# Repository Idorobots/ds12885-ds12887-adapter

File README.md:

# DS12885 -> DS12887 adapter

Ever needed to retrofit a DS1285 compatible RTC in a DS1287 compatible slot? This board's got you covered.

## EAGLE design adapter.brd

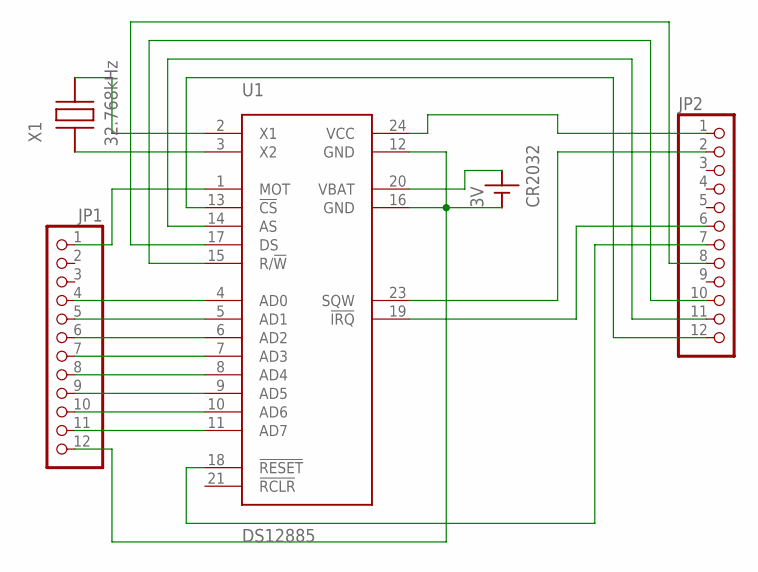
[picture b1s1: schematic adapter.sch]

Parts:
3V: CR2032; CR2032H
JP1, JP2: PINHD-1X12; 1X12
U1: DS12885; DIP24
X1: 32.768kHz; 2PAD

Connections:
GND: 3V.- (GND), JP1.12, U1.12 (GND), U1.16 (GND)
unnamed: U1.3 (X2), X1.2 (X1)
unnamed: U1.2 (X1), X1.1 (X2)
unnamed: JP1.1, U1.1 (MOT)
unnamed: JP1.4, U1.4 (AD0)
unnamed: JP1.5, U1.5 (AD1)
unnamed: JP1.6, U1.6 (AD2)
unnamed: JP1.7, U1.7 (AD3)
unnamed: JP1.8, U1.8 (AD4)
unnamed: JP1.9, U1.9 (AD5)
unnamed: JP1.10, U1.10 (AD6)
unnamed: JP1.11, U1.11 (AD7)
unnamed: 3V.+ (VCC), U1.20 (VBAT)
unnamed: JP2.1, U1.24 (VCC)
unnamed: JP2.2, U1.23 (SQW)
unnamed: JP2.6, U1.19 (!IRQ!)
unnamed: JP2.7, U1.18 (!RESET!)
unnamed: JP2.11, U1.14 (AS)
unnamed: JP2.12, U1.13 (!CS!)
unnamed: JP2.10, U1.15 (R/!W!)
unnamed: JP2.8, U1.17 (DS)

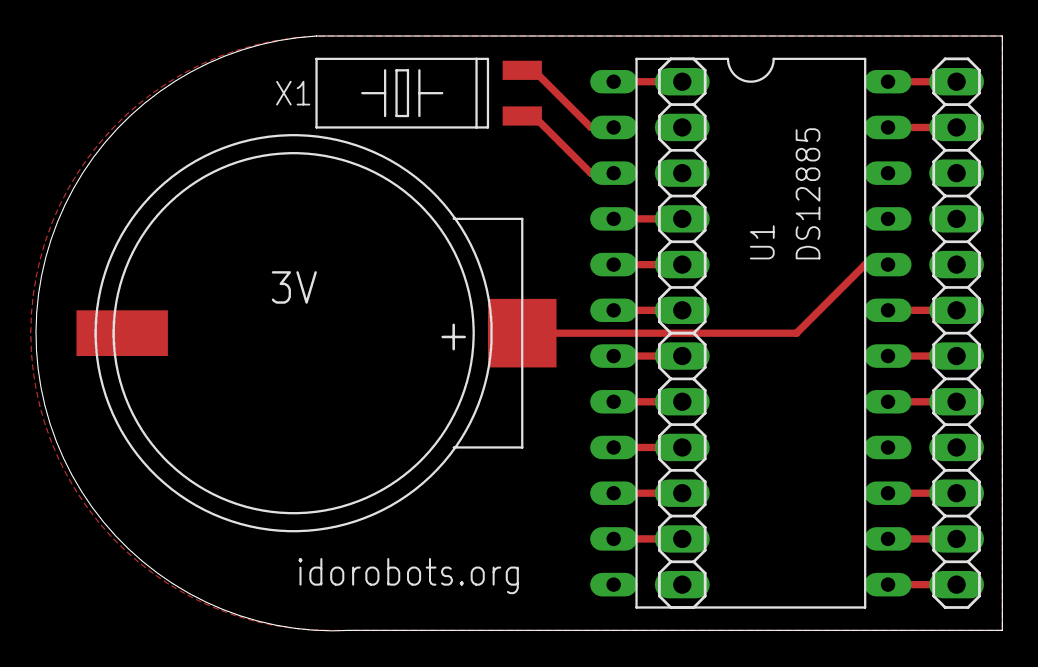
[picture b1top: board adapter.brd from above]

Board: 2 copper layers, 53.7 x 33.0 mm, 5 parts (0 on the bottom side), 21 nets.

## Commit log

2016-04-16 Added RTC library containing the DS12885.
2016-04-16 Added RTC crystal to the library.
2016-04-16 Added a CR2032 battery holder to the library.
2016-04-16 Added the adapter schematic.
2016-04-16 Added the adapter PCB design.
2016-04-16 Added .gitignore.
2016-04-16 Added a README.
2016-04-17 Made PCB border smaller.
2016-04-18 Added an image of the PCB in action.
